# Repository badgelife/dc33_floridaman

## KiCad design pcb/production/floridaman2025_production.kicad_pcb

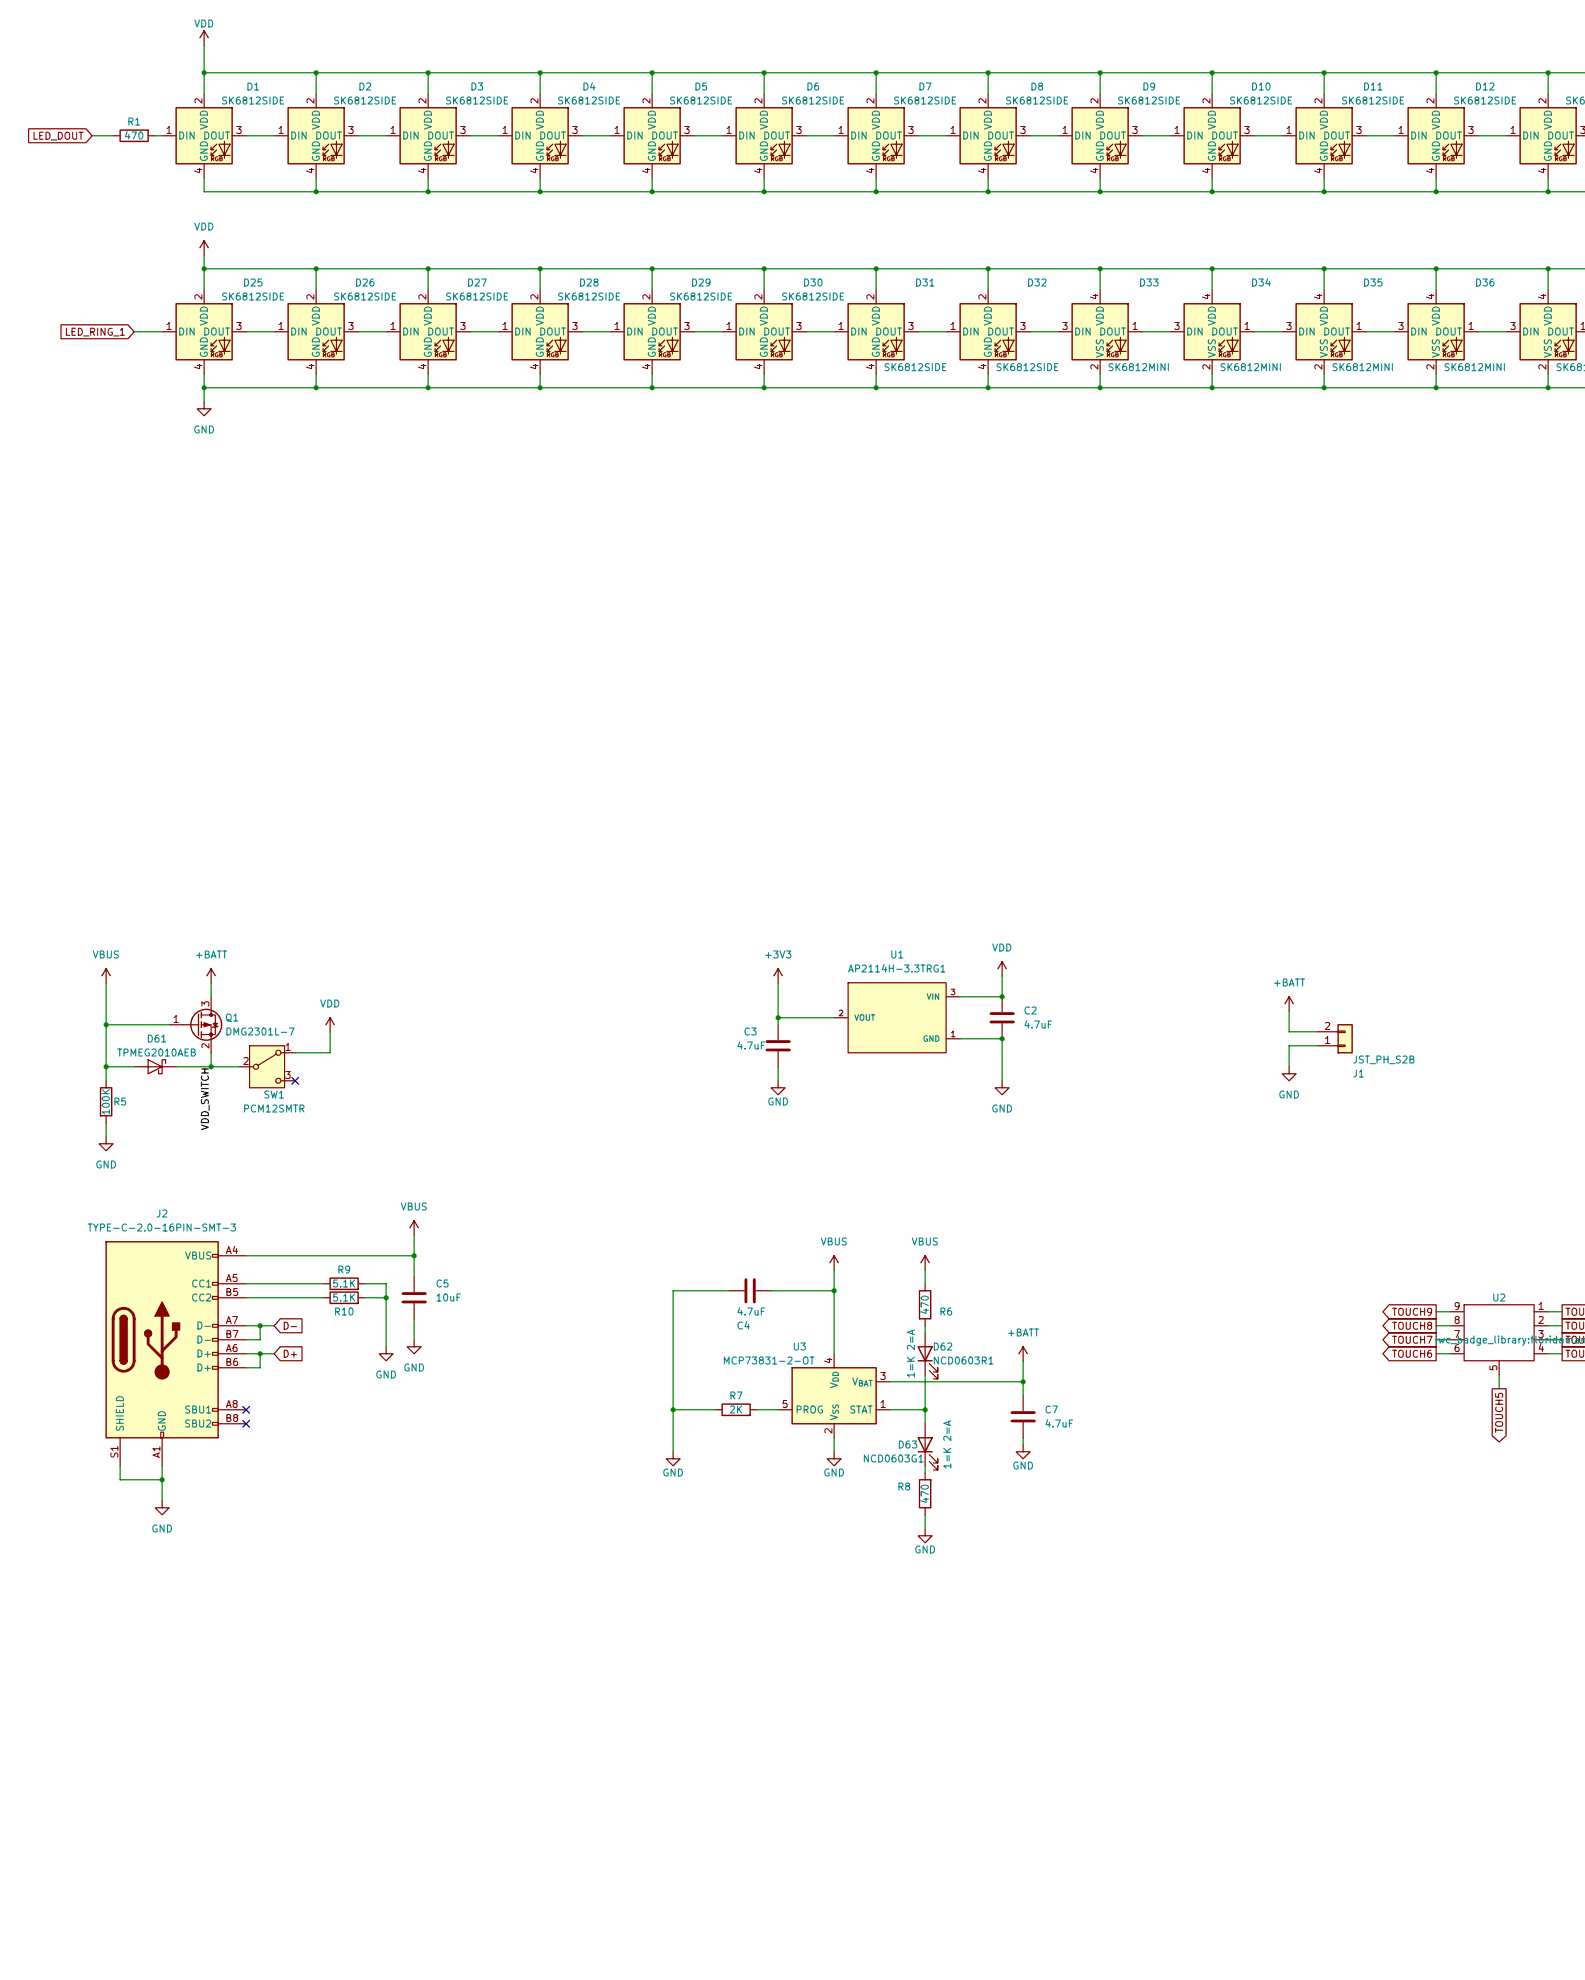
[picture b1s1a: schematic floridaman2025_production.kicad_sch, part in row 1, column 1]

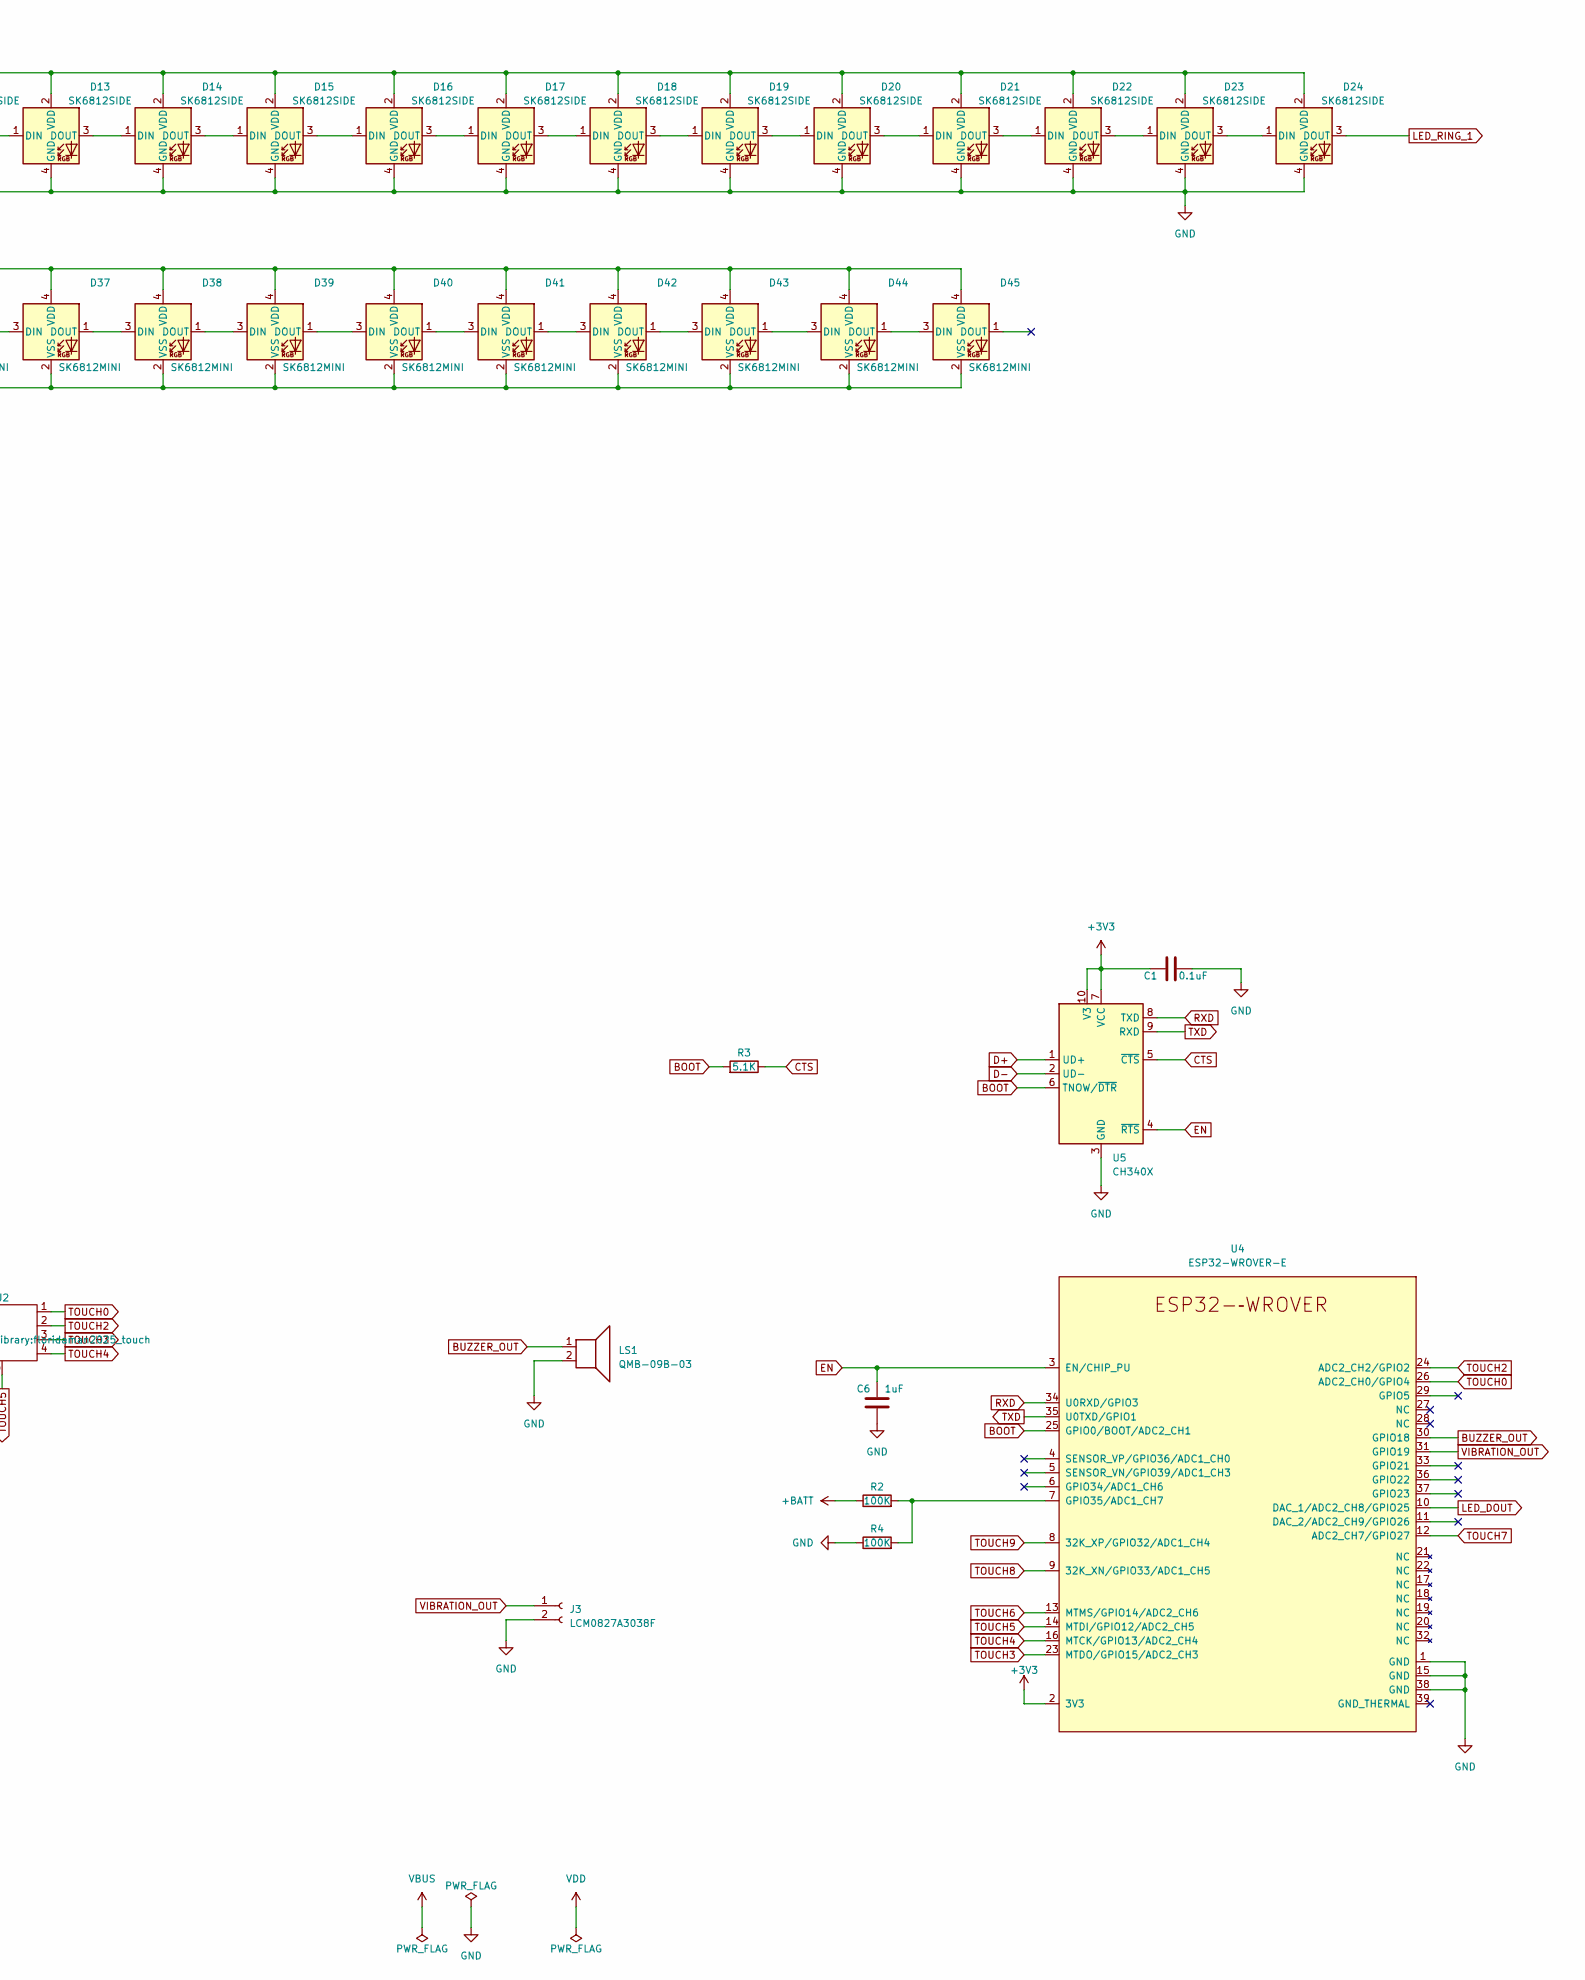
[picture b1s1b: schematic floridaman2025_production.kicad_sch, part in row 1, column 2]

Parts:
C1: 0.1uF; C_0603_1608Metric_Pad1.08x0.95mm_HandSolder
C2, C3, C4, C7: 4.7uF; C_0603_1608Metric_Pad1.08x0.95mm_HandSolder
C5: 10uF; C_0603_1608Metric_Pad1.08x0.95mm_HandSolder
C6: 1uF; C_0603_1608Metric_Pad1.08x0.95mm_HandSolder
D1, D2, D3, D4, D5, D6, D7, D8, D9, D10, D11, D12, D13, D14, D15, D16, D17, D18, D19, D20, D21, D22, D23, D24, D25, D26, D27, D28, D29, D30, D31, D32: SK6812SIDE
D33, D34, D35, D36, D37, D38, D39, D40, D41, D42, D43, D44, D45: SK6812MINI
D61: TPMEG2010AEB; D_SOD-523
D62: NCD0603R1; LED_0603_1608Metric_Pad1.05x0.95mm_HandSolder
D63: NCD0603G1; LED_0603_1608Metric_Pad1.05x0.95mm_HandSolder
J1: JST_PH_S2B; JST_PH_S2B-PH-K_1x02_P2.00mm_Horizontal
J2: TYPE-C-2.0-16PIN-SMT-3
J3: LCM0827A3038F; SolderWire-0.1sqmm_1x02_P3.6mm_D0.4mm_OD1mm
LS1: QMB-09B-03
Q1: DMG2301L-7; SOT-23
R1, R6, R8: 470; R_0603_1608Metric_Pad0.98x0.95mm_HandSolder
R2, R4, R5: 100K; R_0603_1608Metric_Pad0.98x0.95mm_HandSolder
R3, R9, R10: 5.1K; R_0603_1608Metric_Pad0.98x0.95mm_HandSolder
R7: 2K; R_0603_1608Metric_Pad0.98x0.95mm_HandSolder
SW1: PCM12SMTR; SW_SPDT_PCM12
U1: AP2114H-3.3TRG1; AP2114H-3.3TRG1-0; voltage 3.3V; mouser part number 621-AP2114H-3.3TRG1; digikey description IC REG LINEAR 3.3V 1A SOT223
U2: floridaman2025_touch
U3: MCP73831-2-OT; SOT-23-5
U4: ESP32-WROVER-E
U5: CH340X; MSOP-10_3x3mm_P0.5mm

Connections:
+3V3: C1.2, C3.1, U1.2 (VOUT), U4.2 (3V3), U5.7 (VCC), U5.10 (V3)
+BATT: C7.1, J1.2, Q1.3 (D), R2.1, U3.3 (V_{BAT})
/VDD_SWITCH: D61.1 (K), Q1.2 (S), SW1.2 (B)
BOOT: R3.2, U4.25 (GPIO0/BOOT/ADC2_CH1), U5.6 (TNOW/~DTR)
BUZZER_OUT: LS1.1, U4.30 (GPIO18)
CTS: R3.1, U5.5 (~CTS)
D+: J2.A6 (D+), J2.B6 (D+), U5.1 (UD+)
D-: J2.A7 (D-), J2.B7 (D-), U5.2 (UD-)
EN: C6.1, U4.3 (EN/CHIP_PU), U5.4 (~RTS)
GND: C1.1, C2.2, C3.2, C4.2, C5.2, C6.2, C7.2, D1.4 (GND), D2.4 (GND), D3.4 (GND), D4.4 (GND), D5.4 (GND), D6.4 (GND), D7.4 (GND), D8.4 (GND), D9.4 (GND), D10.4 (GND), D11.4 (GND), D12.4 (GND), D13.4 (GND), D14.4 (GND), D15.4 (GND), D16.4 (GND), D17.4 (GND), D18.4 (GND), D19.4 (GND), D20.4 (GND), D21.4 (GND), D22.4 (GND), D23.4 (GND), D24.4 (GND), D25.4 (GND), D26.4 (GND), D27.4 (GND), D28.4 (GND), D29.4 (GND), D30.4 (GND), D31.4 (GND), D32.4 (GND), D33.2 (VSS), D34.2 (VSS), D35.2 (VSS), D36.2 (VSS), D37.2 (VSS), D38.2 (VSS), D39.2 (VSS), D40.2 (VSS), D41.2 (VSS), D42.2 (VSS), D43.2 (VSS), D44.2 (VSS), D45.2 (VSS), J1.1, J2.A1 (GND), J2.A12 (GND), J2.B1 (GND), J2.B12 (GND), J2.S1 (SHIELD), J3.2, LS1.2, R4.1, R5.2, R7.1, R8.1, R9.2, R10.2, U1.1 (GND), U3.2 (V_{SS}), U4.1 (GND), U4.15 (GND), U4.38 (GND), U5.3 (GND)
LED_RING_1: D24.3 (DOUT), D25.1 (DIN)
unnamed: D1.3 (DOUT), D2.1 (DIN)
unnamed: D2.3 (DOUT), D3.1 (DIN)
unnamed: D3.3 (DOUT), D4.1 (DIN)
unnamed: D4.3 (DOUT), D5.1 (DIN)
unnamed: D5.3 (DOUT), D6.1 (DIN)
unnamed: D6.3 (DOUT), D7.1 (DIN)
unnamed: D7.3 (DOUT), D8.1 (DIN)
unnamed: D8.3 (DOUT), D9.1 (DIN)
unnamed: D9.3 (DOUT), D10.1 (DIN)
unnamed: D10.3 (DOUT), D11.1 (DIN)
unnamed: D11.3 (DOUT), D12.1 (DIN)
unnamed: D12.3 (DOUT), D13.1 (DIN)
unnamed: D13.3 (DOUT), D14.1 (DIN)
unnamed: D14.3 (DOUT), D15.1 (DIN)
unnamed: D15.3 (DOUT), D16.1 (DIN)
unnamed: D16.3 (DOUT), D17.1 (DIN)
unnamed: D17.3 (DOUT), D18.1 (DIN)
unnamed: D18.3 (DOUT), D19.1 (DIN)
unnamed: D19.3 (DOUT), D20.1 (DIN)
unnamed: D20.3 (DOUT), D21.1 (DIN)
unnamed: D21.3 (DOUT), D22.1 (DIN)
unnamed: D22.3 (DOUT), D23.1 (DIN)
unnamed: D23.3 (DOUT), D24.1 (DIN)
unnamed: D25.3 (DOUT), D26.1 (DIN)
unnamed: D26.3 (DOUT), D27.1 (DIN)
unnamed: D27.3 (DOUT), D28.1 (DIN)
unnamed: D28.3 (DOUT), D29.1 (DIN)
unnamed: D29.3 (DOUT), D30.1 (DIN)
unnamed: D30.3 (DOUT), D31.1 (DIN)
unnamed: D31.3 (DOUT), D32.1 (DIN)
unnamed: D32.3 (DOUT), D33.3 (DIN)
unnamed: D33.1 (DOUT), D34.3 (DIN)
unnamed: D34.1 (DOUT), D35.3 (DIN)
unnamed: D35.1 (DOUT), D36.3 (DIN)
unnamed: D36.1 (DOUT), D37.3 (DIN)
unnamed: D37.1 (DOUT), D38.3 (DIN)
unnamed: D38.1 (DOUT), D39.3 (DIN)
unnamed: D39.1 (DOUT), D40.3 (DIN)
unnamed: D40.1 (DOUT), D41.3 (DIN)
unnamed: D41.1 (DOUT), D42.3 (DIN)
unnamed: D42.1 (DOUT), D43.3 (DIN)
unnamed: D43.1 (DOUT), D44.3 (DIN)
unnamed: D44.1 (DOUT), D45.3 (DIN)
unnamed: D62.2 (A), R6.2
unnamed: D62.1 (K), D63.2 (A), U3.1 (STAT)
unnamed: D63.1 (K), R8.2
unnamed: J2.A5 (CC1), R9.1
unnamed: J2.B5 (CC2), R10.1
unnamed: R7.2, U3.5 (PROG)
unnamed: R2.2, R4.2, U4.7 (GPIO35/ADC1_CH7)
RXD: U4.34 (U0RXD/GPIO3), U5.8 (TXD)
TOUCH0: U2.1, U4.26 (ADC2_CH0/GPIO4)
TOUCH2: U2.2, U4.24 (ADC2_CH2/GPIO2)
TOUCH3: U2.3, U4.23 (MTDO/GPIO15/ADC2_CH3)
TOUCH4: U2.4, U4.16 (MTCK/GPIO13/ADC2_CH4)
TOUCH5: U2.5, U4.14 (MTDI/GPIO12/ADC2_CH5)
TOUCH6: U2.6, U4.13 (MTMS/GPIO14/ADC2_CH6)
TOUCH7: U2.7, U4.12 (ADC2_CH7/GPIO27)
TOUCH8: U2.8, U4.9 (32K_XN/GPIO33/ADC1_CH5)
TOUCH9: U2.9, U4.8 (32K_XP/GPIO32/ADC1_CH4)
TXD: U4.35 (U0TXD/GPIO1), U5.9 (RXD)
VBUS: C4.1, C5.1, D61.2 (A), J2.A4 (VBUS), J2.A9 (VBUS), J2.B4 (VBUS), J2.B9 (VBUS), Q1.1 (G), R5.1, R6.1, U3.4 (V_{DD})
VDD: C2.1, D1.2 (VDD), D2.2 (VDD), D3.2 (VDD), D4.2 (VDD), D5.2 (VDD), D6.2 (VDD), D7.2 (VDD), D8.2 (VDD), D9.2 (VDD), D10.2 (VDD), D11.2 (VDD), D12.2 (VDD), D13.2 (VDD), D14.2 (VDD), D15.2 (VDD), D16.2 (VDD), D17.2 (VDD), D18.2 (VDD), D19.2 (VDD), D20.2 (VDD), D21.2 (VDD), D22.2 (VDD), D23.2 (VDD), D24.2 (VDD), D25.2 (VDD), D26.2 (VDD), D27.2 (VDD), D28.2 (VDD), D29.2 (VDD), D30.2 (VDD), D31.2 (VDD), D32.2 (VDD), D33.4 (VDD), D34.4 (VDD), D35.4 (VDD), D36.4 (VDD), D37.4 (VDD), D38.4 (VDD), D39.4 (VDD), D40.4 (VDD), D41.4 (VDD), D42.4 (VDD), D43.4 (VDD), D44.4 (VDD), D45.4 (VDD), SW1.1 (A), U1.3 (VIN)
VIBRATION_OUT: J3.1, U4.31 (GPIO19)

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
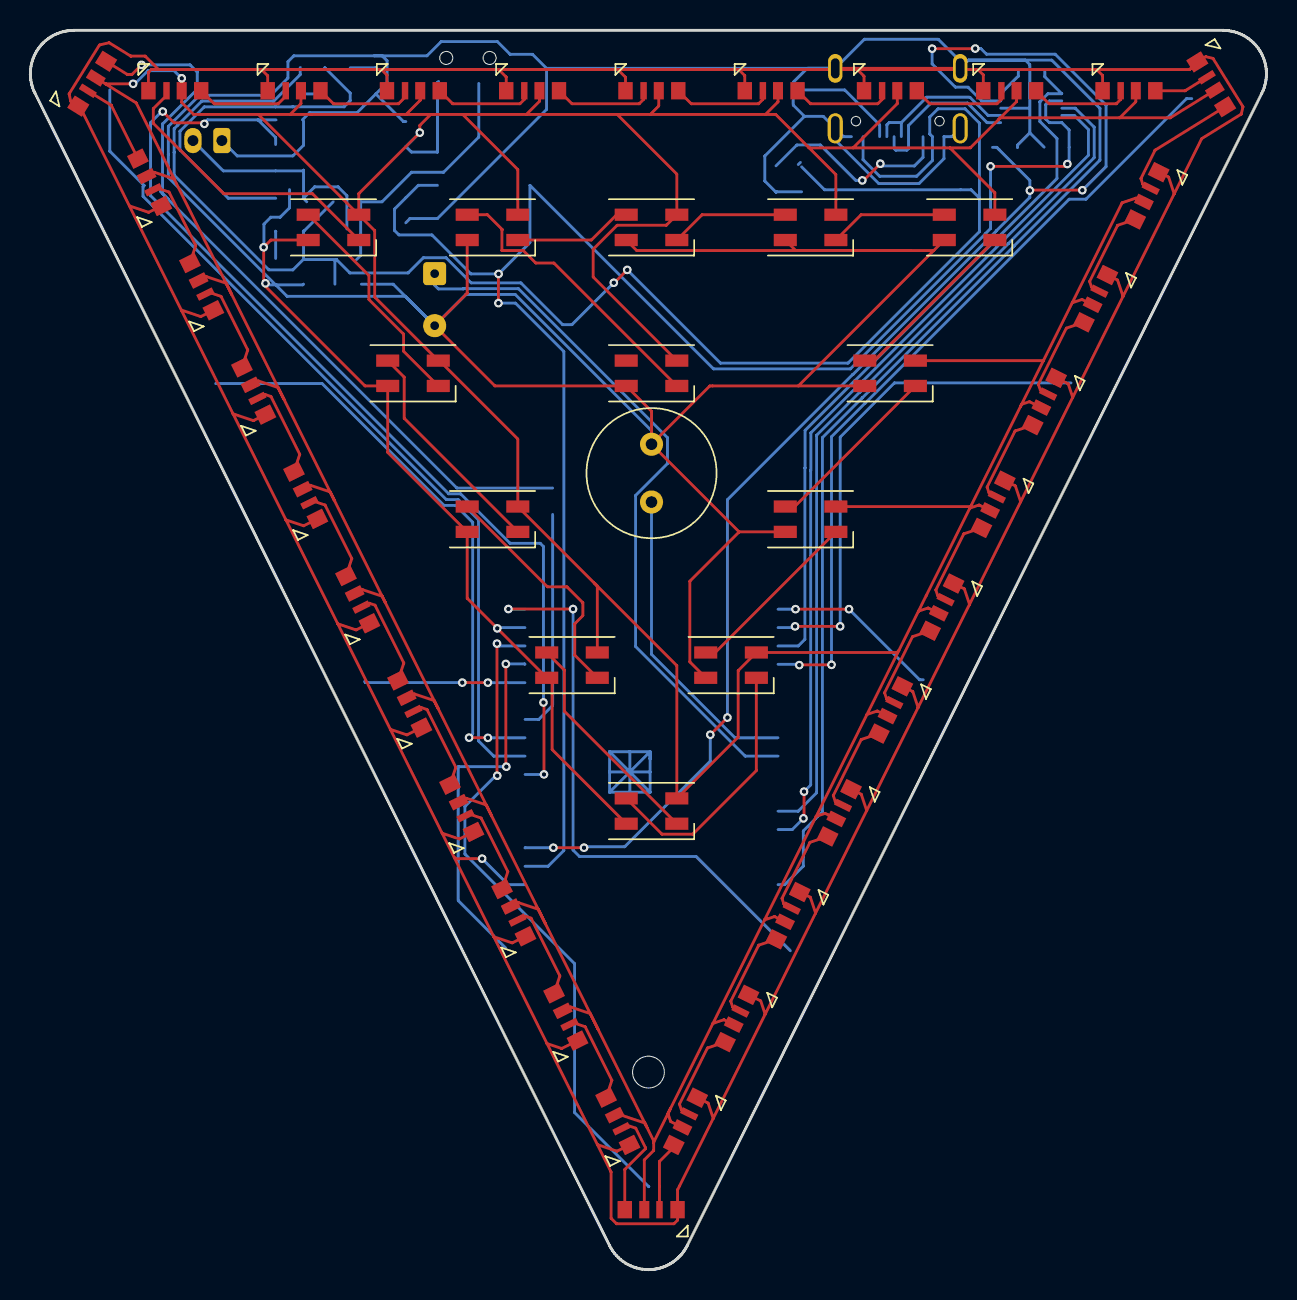
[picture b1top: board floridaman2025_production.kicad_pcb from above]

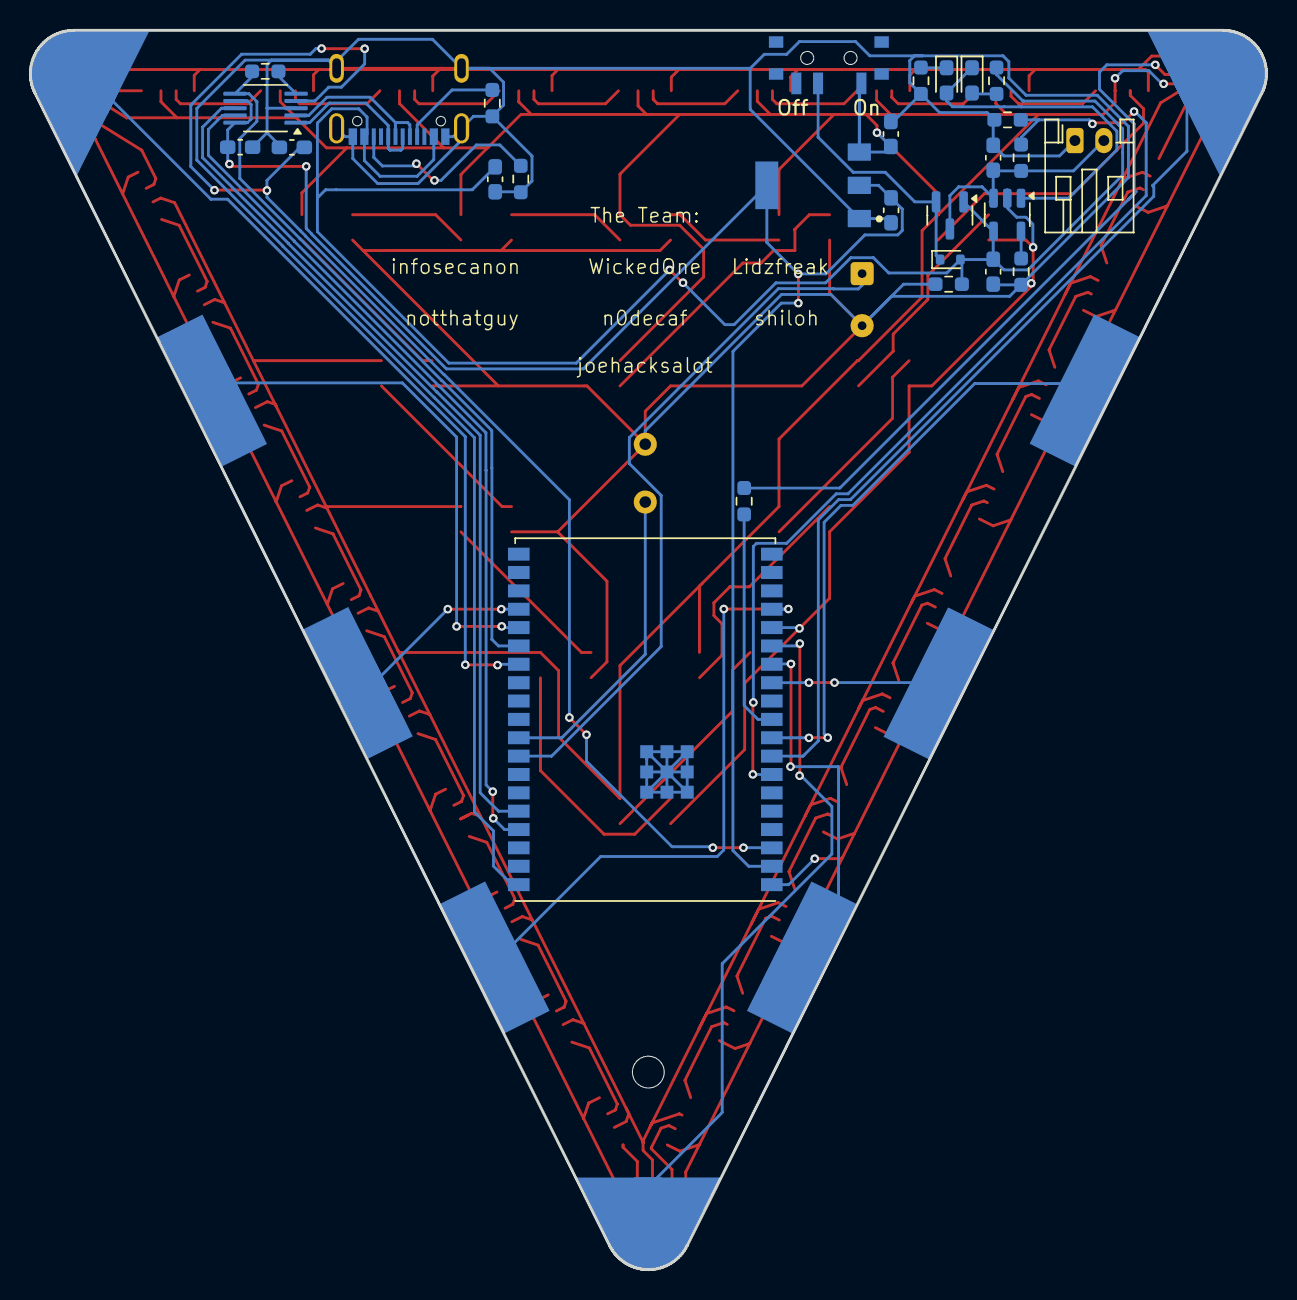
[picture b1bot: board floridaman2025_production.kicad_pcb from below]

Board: 2 copper layers, 85.5 x 85.7 mm, 76 parts (30 on the bottom side), 77 nets.

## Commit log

2025-08-07 Introduction
